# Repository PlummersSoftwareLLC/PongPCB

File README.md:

# PongPCB
This is a KiCad project and Gerber files for Pong Composite Video replacement PCB, as featured in the original [Dave's Garage episode](https://youtu.be/iF7lo0vU_WI).

In theory you should be able to order a board from JLCPCB using just the Gerber files (specifically, the already-packed 'Archive.zip' in the Gerbers folder). 
Or you could use KiCad to load the project and generate your own Gerber and Drill files.

A list of the components that need to be soldered onto the PCB is included in [PARTSLIST.md](PARTSLIST.md). A list of other components is included in the video description on YouTube.

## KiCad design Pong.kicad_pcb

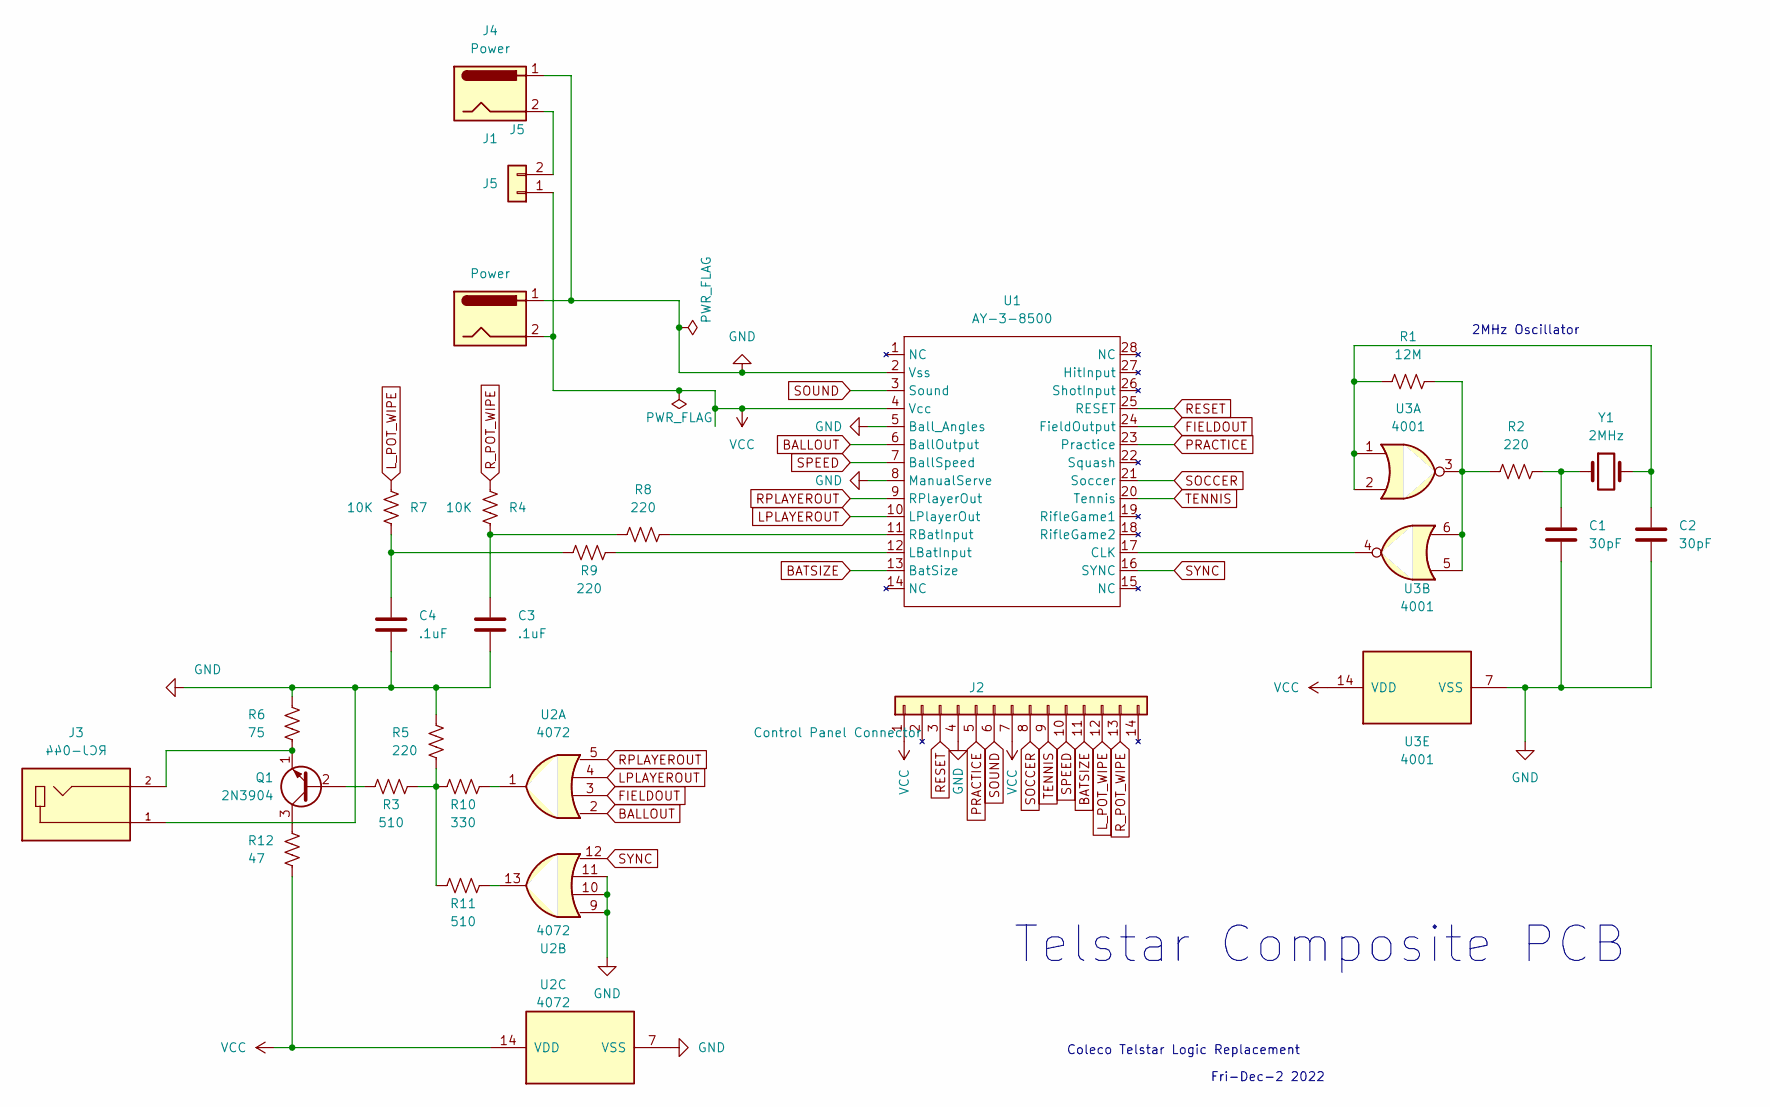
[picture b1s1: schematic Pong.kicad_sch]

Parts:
C1, C2: 30pF; C_Disc_D8.0mm_W5.0mm_P7.50mm
C3, C4: .1uF; C_Disc_D8.0mm_W5.0mm_P7.50mm
J1, J4: Power; BarrelJack_CUI_PJ-063AH_Horizontal
J2: Control Panel Connector; Molex_KK-254_AE-6410-14A_1x14_P2.54mm_Vertical
J3: RCJ-044; CUI_RCJ-044; PARTREV 1.02
J5: J5; PinHeader_1x02_P1.27mm_Horizontal
Q1: 2N3904; TO-92_Inline
R1: 12M; R_Axial_DIN0309_L9.0mm_D3.2mm_P12.70mm_Horizontal
R2, R5, R8, R9: 220; R_Axial_DIN0309_L9.0mm_D3.2mm_P12.70mm_Horizontal
R3, R11: 510; R_Axial_DIN0309_L9.0mm_D3.2mm_P12.70mm_Horizontal
R4, R7: 10K; R_Axial_DIN0309_L9.0mm_D3.2mm_P12.70mm_Horizontal
R6: 75; R_Axial_DIN0309_L9.0mm_D3.2mm_P12.70mm_Horizontal
R10: 330; R_Axial_DIN0309_L9.0mm_D3.2mm_P12.70mm_Horizontal
R12: 47; R_Axial_DIN0309_L9.0mm_D3.2mm_P12.70mm_Horizontal
U1: AY-3-8500; DIP-28_W15.24mm_Socket_LongPads
U2: 4072; DIP-14_W7.62mm_Socket_LongPads
U3: 4001; DIP-14_W7.62mm_Socket_LongPads
Y1: 2MHz; Crystal_HC52-8mm_Horizontal

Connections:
BALLOUT: U1.6 (BallOutput), U2.2
BATSIZE: J2.11, U1.13 (BatSize)
FIELDOUT: U1.24 (FieldOutput), U2.3
GND: C1.2, C2.2, C3.2, C4.2, J1.1, J2.4, J3.1, J4.1, R5.1, R6.1, U1.2 (Vss), U1.5 (Ball_Angles), U1.8 (ManualServe), U2.7 (VSS), U2.9, U2.10, U2.11, U3.7 (VSS)
LPLAYEROUT: U1.10 (LPlayerOut), U2.4
L_POT_WIPE: J2.12, R7.1
unnamed: C1.1, R2.2, Y1.1
unnamed: C2.1, R1.1, U3.1, U3.2, Y1.2
unnamed: C4.1, R7.2, R9.1
unnamed: J3.2, Q1.1 (E), R6.2
unnamed: J4.2, J5.2
unnamed: Q1.2 (B), R3.1
unnamed: Q1.3 (C), R12.1
unnamed: R1.2, R2.1, U3.3, U3.5, U3.6
unnamed: C3.1, R4.2, R8.1
unnamed: R8.2, U1.11 (RBatInput)
unnamed: R9.2, U1.12 (LBatInput)
unnamed: R3.2, R5.2, R10.1, R11.1
unnamed: R10.2, U2.1
unnamed: R11.2, U2.13
unnamed: U1.17 (CLK), U3.4
PRACTICE: J2.5, U1.23 (Practice)
RESET: J2.3, U1.25 (RESET)
RPLAYEROUT: U1.9 (RPlayerOut), U2.5
R_POT_WIPE: J2.13, R4.1
SOCCER: J2.8, U1.21 (Soccer)
SOUND: J2.6, U1.3 (Sound)
SPEED: J2.10, U1.7 (BallSpeed)
SYNC: U1.16 (SYNC), U2.12
TENNIS: J2.9, U1.20 (Tennis)
VCC: J1.2, J2.1, J2.7, J5.1, R12.2, U1.4 (Vcc), U2.14 (VDD), U3.14 (VDD)

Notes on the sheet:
Coleco Telstar Logic Replacement
Fri-Dec-2 2022
2MHz Oscillator
Telstar Composite PCB

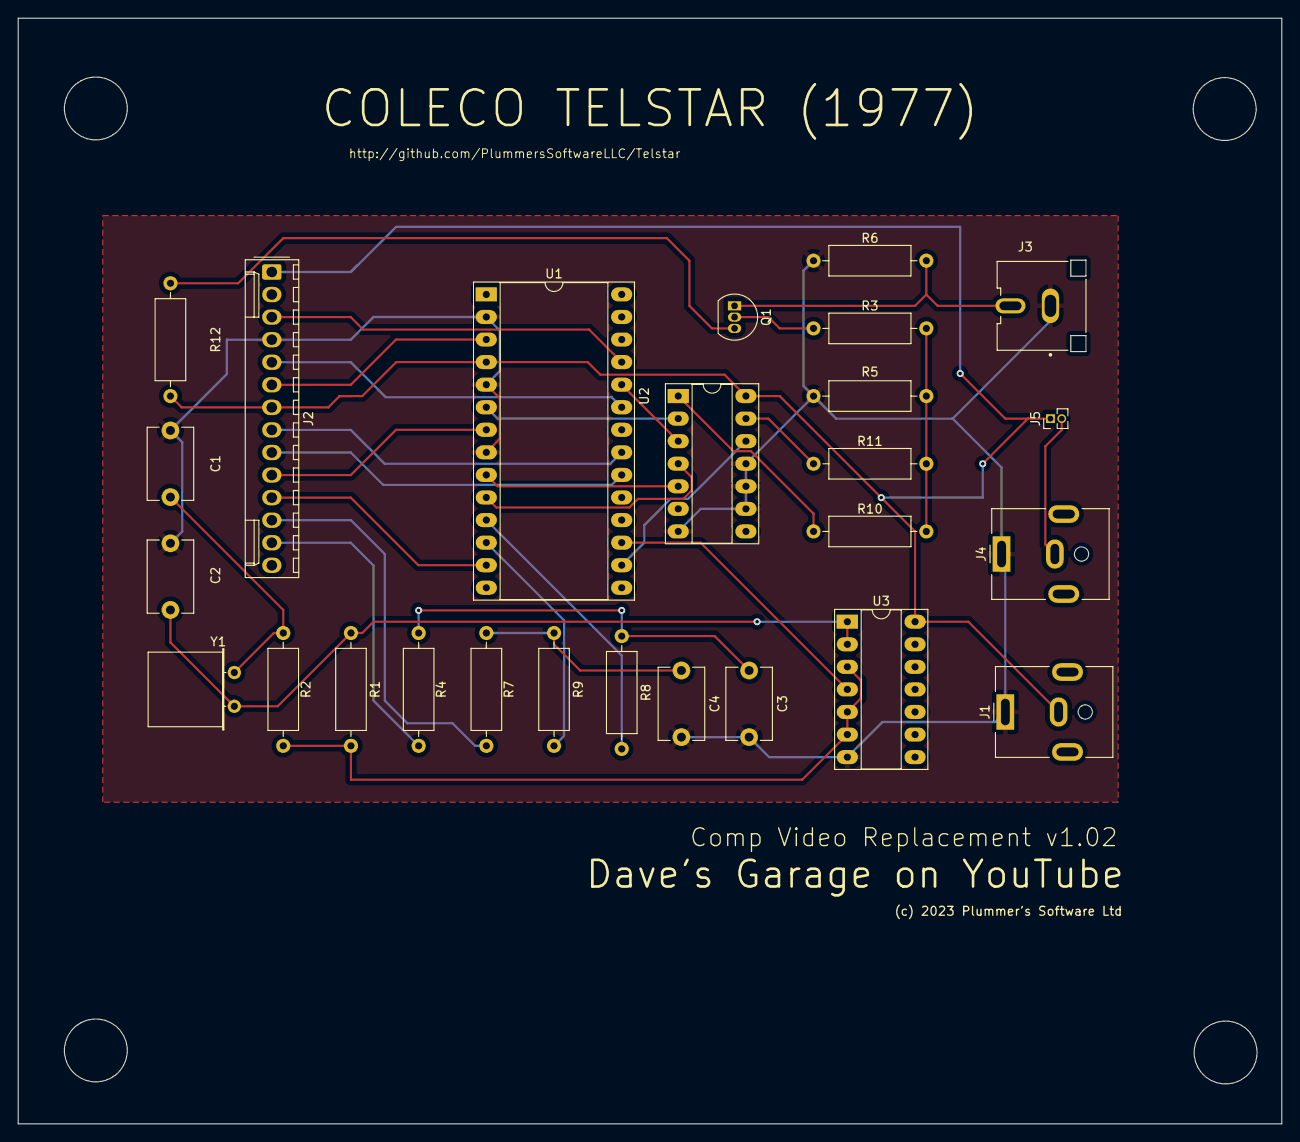
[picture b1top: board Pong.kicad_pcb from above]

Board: 2 copper layers, 142.2 x 124.5 mm, 26 parts (0 on the bottom side), 31 nets.

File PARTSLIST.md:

# Parts list

Below is the list of components that need to be installed onto the PCB, as indicated on the PCB design. A list of (other) components with purchase links is already available in the [YouTube video](https://youtu.be/iF7lo0vU_WI) description. The links in the table below are to reference information only.

| Category | Value/type | Quantity | Board location(s) | Notes |
|-|-|-|-|-|
| Capacitor | 30pF | 2 | C1, C2 | |
| Capacitor | 0.1&#181;F | 2 | C3, C4 | |
| Crystal oscillator | HC49U 2.0MHz, or equivalent | 1 | Y1 | Oscillators are available in a wide range of frequencies, make sure to get the 2.0 MHz type! |
| DC barrel power connector | horizontal | 2 | J1, J4 | |
| IC | [AY-3-8500](https://en.wikipedia.org/wiki/AY-3-8500) | 1 | U1 | Has to be taken from the Coleco Telstar PCB, or another system that's based on it. If sockets are used, this IC must not be soldered but inserted into the socket after that has been soldered in. |
| IC | DIL-14 [4001](https://en.wikibooks.org/wiki/Practical_Electronics/IC/4001) | 1 | U3 | Can be taken from the Coleco Telstar PCB. If buying separately, note that a surface-mount version (SOIC-14) is also available that won't work for this build. If sockets are used, this IC must not be soldered but inserted into the socket after that has been soldered in. |
| IC | DIL-14 [4072](https://en.wikibooks.org/wiki/Practical_Electronics/IC/4072) | 1 | U2 | Can be taken from the Coleco Telstar PCB. If buying separately, note that a surface-mount version (SOIC-14) is also available that won't work for this build. If sockets are used, this IC must not be soldered but inserted into the socket after that has been soldered in. |
| Pin header | 2 pins | 1 | J5 | |
| Pin header | 14 pins | 1 | J2 | |
| RCA connector | RCJ-044 | 1 | J3 | |
| Resistor | 47&#8486; | 1 | R12 | |
| Resistor | 75&#8486; | 1 | R6 | |
| Resistor | 220&#8486; | 4 | R2, R5, R8, R9 | |
| Resistor | 330&#8486; | 1 | R10 | |
| Resistor | 510&#8486; | 2 | R3, R11 | |
| Resistor | 10K&#8486; | 2 | R4, R7 | |
| Resistor | 12M&#8486; | 1 | R1 | |
| Socket | 14 pins | 2 | U2, U3 | Use of sockets is recommended, but strictly speaking optional. |
| Socket | 28 pins | 1 | U1 | Use of sockets is recommended, but strictly speaking optional. |
| Transistor | [2N3904](https://en.wikipedia.org/wiki/2N3904) | 1 | Q1 | |

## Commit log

2023-01-25 Initial commit from episode
2023-01-25 Add video image to README
2023-01-26 Add GPLv3 licence file
2023-01-28 Add parts list
2023-01-28 Add link to parts list in README.
2023-02-11 Fix typo

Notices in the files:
Pong.kicad_pcb:
(c) 2023 Plummer's Software Ltd
